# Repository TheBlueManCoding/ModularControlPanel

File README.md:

# ModularControlPanel
Mechanics, PCB and Software for my modular control panel that is used with my cnc machine driven by LinuxCnc

If you need the mechanic parts, just open an issue and tell me.

This bboard delivers:
- 12 Key inputs
- 8 LED outputs driven by 2 boards of these: https://aliexpress.com/item/1005003772569293.html
- 3 ADC inputs
- directly routed inputs for connection to the control cabinet (connected via 15 Pin cable):
  - POWER_KEY or the standby Variant POWER_KEY_MAN, both enable POWER_EN 
  - START_KEY, STOP_KEY, BREAK_KEY
  - input for the ESTOP_LED
  - ESTOP connector
  - 3 Reserve lines
- I2C extension connectors for 3.3 and 5V I2C
- ws28 smart LED connector
- one connector for a MIST System (see https://github.com/TheBlueManCoding/WemosMosfet)

all switches are connected by:
- https://aliexpress.com/item/4000502453714.html
- https://aliexpress.com/item/1005001317075834.html

## Front view of the control panel mockup:

#PCB with some connected switches, leds and the mist cooling controller

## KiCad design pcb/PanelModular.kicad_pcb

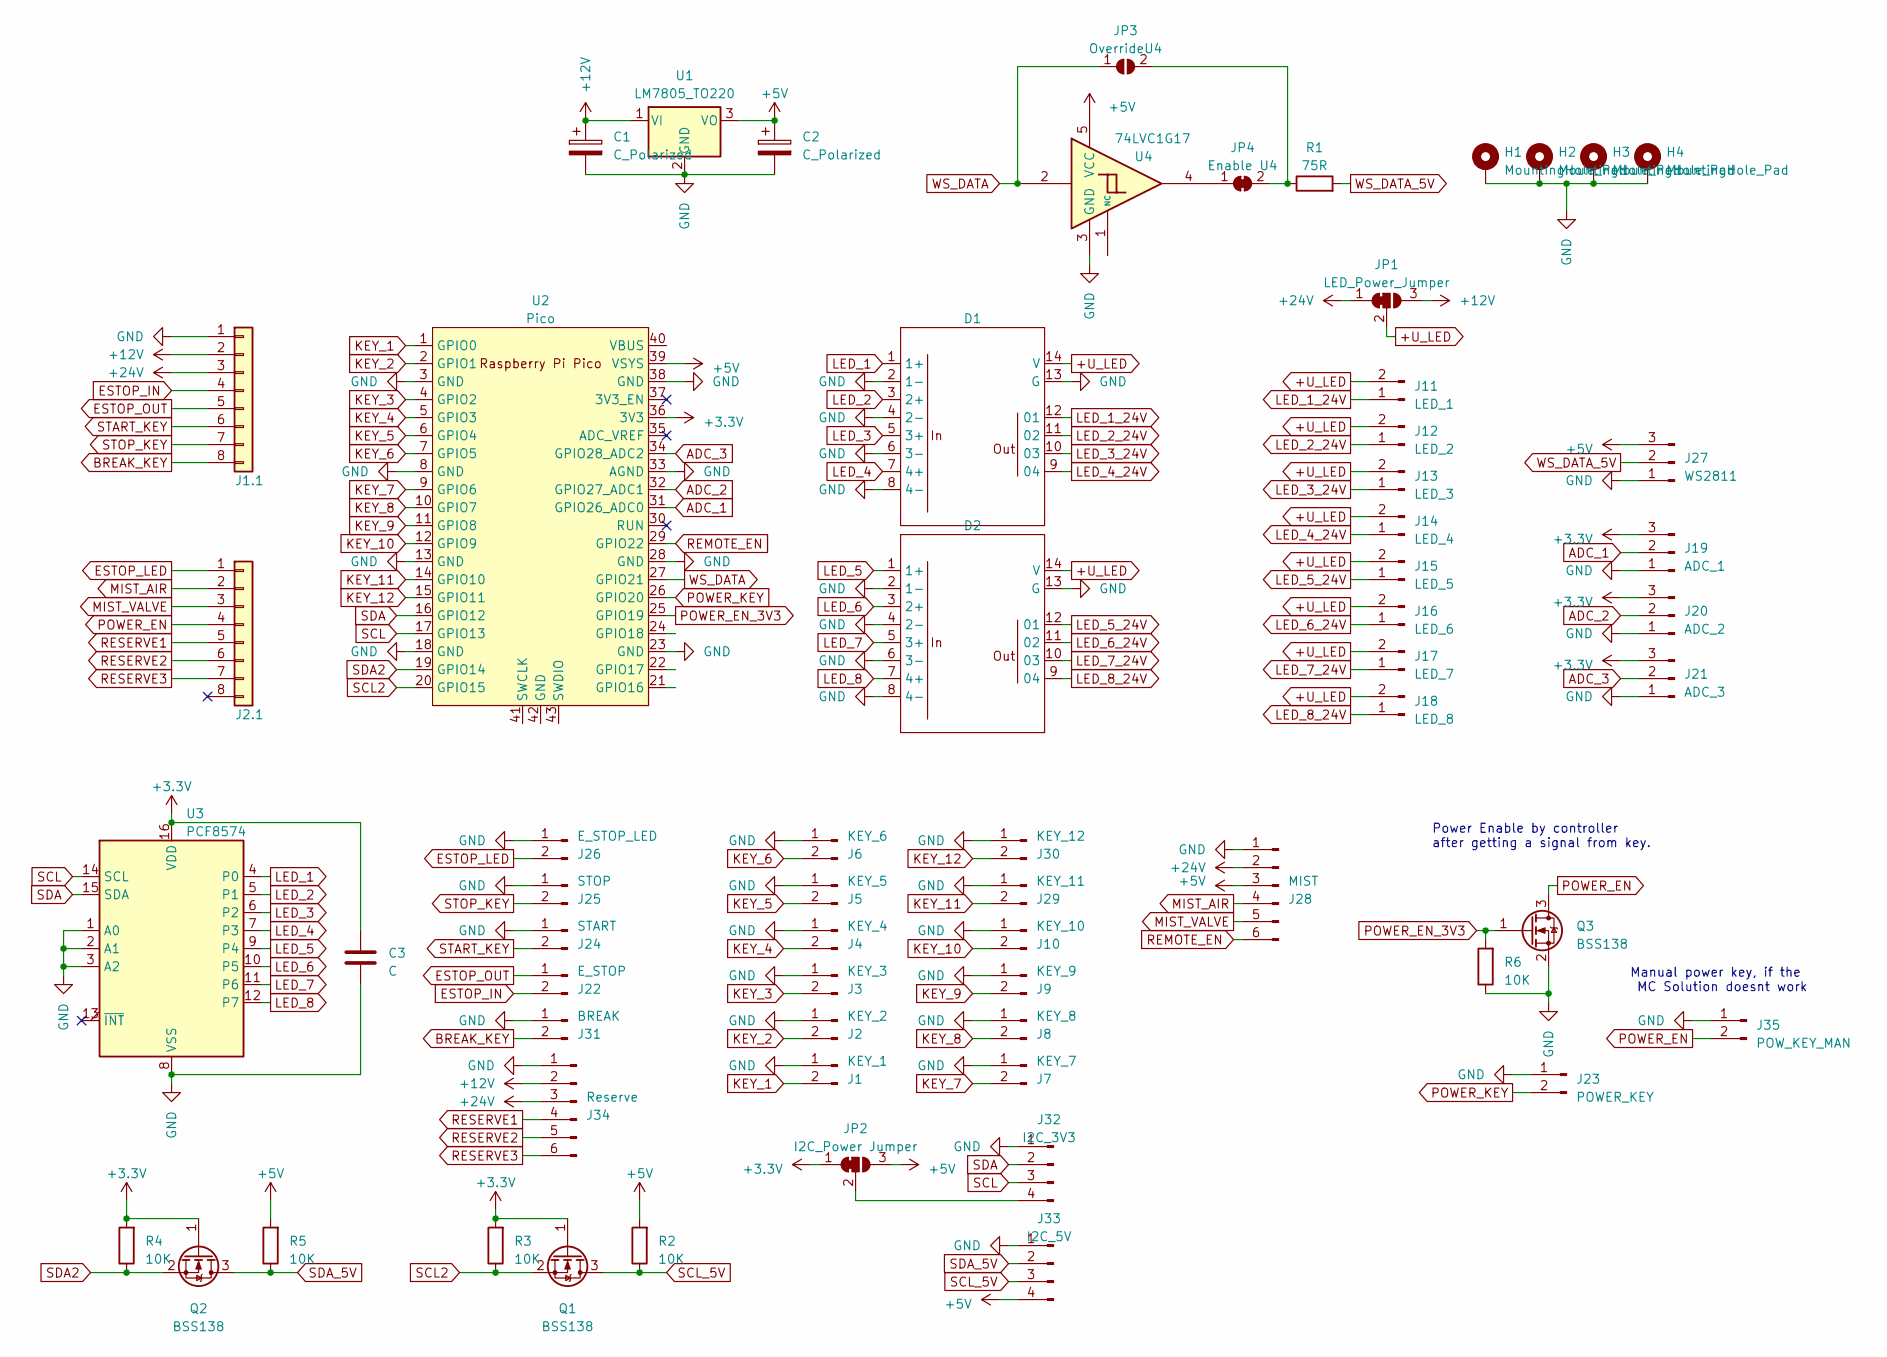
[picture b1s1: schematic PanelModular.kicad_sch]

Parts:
C1, C2: C_Polarized; CP_EIA-6032-28_Kemet-C_Pad2.25x2.35mm_HandSolder
C3: C; C_0805_2012Metric_Pad1.18x1.45mm_HandSolder
D1, D2: OP714A04
H1, H2, H3, H4: MountingHole_Pad; MountingHole_4.3mm_M4_Pad
J1: KEY_1; JST_XH_B2B-XH-A_1x02_P2.50mm_Vertical
J1.1, J2.1: Conn_01x08; TerminalBlock_WAGO_236-408_1x08_P5.00mm_45Degree
J2: KEY_2; JST_XH_B2B-XH-A_1x02_P2.50mm_Vertical
J3: KEY_3; JST_XH_B2B-XH-A_1x02_P2.50mm_Vertical
J4: KEY_4; JST_XH_B2B-XH-A_1x02_P2.50mm_Vertical
J5: KEY_5; JST_XH_B2B-XH-A_1x02_P2.50mm_Vertical
J6: KEY_6; JST_XH_B2B-XH-A_1x02_P2.50mm_Vertical
J7: KEY_7; JST_XH_B2B-XH-A_1x02_P2.50mm_Vertical
J8: KEY_8; JST_XH_B2B-XH-A_1x02_P2.50mm_Vertical
J9: KEY_9; JST_XH_B2B-XH-A_1x02_P2.50mm_Vertical
J10: KEY_10; JST_XH_B2B-XH-A_1x02_P2.50mm_Vertical
J11: LED_1; JST_XH_B2B-XH-A_1x02_P2.50mm_Vertical
J12: LED_2; JST_XH_B2B-XH-A_1x02_P2.50mm_Vertical
J13: LED_3; JST_XH_B2B-XH-A_1x02_P2.50mm_Vertical
J14: LED_4; JST_XH_B2B-XH-A_1x02_P2.50mm_Vertical
J15: LED_5; JST_XH_B2B-XH-A_1x02_P2.50mm_Vertical
J16: LED_6; JST_XH_B2B-XH-A_1x02_P2.50mm_Vertical
J17: LED_7; JST_XH_B2B-XH-A_1x02_P2.50mm_Vertical
J18: LED_8; JST_XH_B2B-XH-A_1x02_P2.50mm_Vertical
J19: ADC_1; JST_XH_B3B-XH-A_1x03_P2.50mm_Vertical
J20: ADC_2; JST_XH_B3B-XH-A_1x03_P2.50mm_Vertical
J21: ADC_3; JST_XH_B3B-XH-A_1x03_P2.50mm_Vertical
J22: E_STOP; JST_XH_B2B-XH-A_1x02_P2.50mm_Vertical
J23: POWER_KEY; JST_XH_B2B-XH-A_1x02_P2.50mm_Vertical
J24: START; JST_XH_B2B-XH-A_1x02_P2.50mm_Vertical
J25: STOP; JST_XH_B2B-XH-A_1x02_P2.50mm_Vertical
J26: E_STOP_LED; JST_XH_B2B-XH-A_1x02_P2.50mm_Vertical
J27: WS2811; JST_XH_B3B-XH-A_1x03_P2.50mm_Vertical
J28: MIST; JST_XH_B6B-XH-A_1x06_P2.50mm_Vertical
J29: KEY_11; JST_XH_B2B-XH-A_1x02_P2.50mm_Vertical
J30: KEY_12; JST_XH_B2B-XH-A_1x02_P2.50mm_Vertical
J31: BREAK; JST_XH_B2B-XH-A_1x02_P2.50mm_Vertical
J32: I2C_3V3; JST_XH_B4B-XH-A_1x04_P2.50mm_Vertical
J33: I2C_5V; JST_XH_B4B-XH-A_1x04_P2.50mm_Vertical
J34: Reserve; JST_XH_B6B-XH-A_1x06_P2.50mm_Vertical
J35: POW_KEY_MAN; JST_XH_B2B-XH-A_1x02_P2.50mm_Vertical
JP1: LED_Power_Jumper; SolderJumper-3_P1.3mm_Bridged12_Pad1.0x1.5mm_NumberLabels
JP2: I2C_Power Jumper; SolderJumper-3_P1.3mm_Bridged12_Pad1.0x1.5mm_NumberLabels
JP3: OverrideU4; SolderJumper-2_P1.3mm_Open_Pad1.0x1.5mm
JP4: Enable U4; SolderJumper-2_P1.3mm_Bridged_Pad1.0x1.5mm
Q1, Q2, Q3: BSS138; SOT-23_Handsoldering
R1: 75R; R_0805_2012Metric_Pad1.20x1.40mm_HandSolder
R2, R3, R4, R5, R6: 10K; R_0805_2012Metric_Pad1.20x1.40mm_HandSolder
U1: LM7805_TO220; TO-220-3_Vertical
U2: Pico; RPi_Pico_SMD_TH
U3: PCF8574; SO-16_7,7x10.2mm_P1.27mm-PCF8574
U4: 74LVC1G17; SOT-23-5_HandSoldering

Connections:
+3.3V: C3.1, J19.3, J20.3, J21.3, JP2.1 (A), Q1.1 (G), Q2.1 (G), R3.2, R4.2, U2.36 (3V3), U3.16 (VDD)
+5V: C2.1, J27.3, J28.3, J33.4, JP2.3 (B), R2.2, R5.2, U1.3 (VO), U2.39 (VSYS), U4.5 (VCC)
+12V: C1.1, J1.1.2, J34.2, JP1.3 (B), U1.1 (VI)
+24V: J1.1.3, J28.2, J34.3, JP1.1 (A)
+U_LED: D1.14 (V), D2.14 (V), J11.2, J12.2, J13.2, J14.2, J15.2, J16.2, J17.2, J18.2, JP1.2 (C)
ADC_1: J19.2, U2.31 (GPIO26_ADC0)
ADC_2: J20.2, U2.32 (GPIO27_ADC1)
ADC_3: J21.2, U2.34 (GPIO28_ADC2)
BREAK_KEY: J1.1.8, J31.2
ESTOP_IN: J1.1.4, J22.2
ESTOP_LED: J2.1.1, J26.2
ESTOP_OUT: J1.1.5, J22.1
GND: C1.2, C2.2, C3.2, D1.2 (1-), D1.4 (2-), D1.6 (3-), D1.8 (4-), D1.13 (G), D2.2 (1-), D2.4 (2-), D2.6 (3-), D2.8 (4-), D2.13 (G), H1.1, H2.1, H3.1, H4.1, J1.1, J1.1.1, J2.1, J3.1, J4.1, J5.1, J6.1, J7.1, J8.1, J9.1, J10.1, J19.1, J20.1, J21.1, J23.1, J24.1, J25.1, J26.1, J27.1, J28.1, J29.1, J30.1, J31.1, J32.1, J33.1, J34.1, J35.1, Q3.2 (S), R6.1, U1.2 (GND), U2.3 (GND), U2.8 (GND), U2.13 (GND), U2.18 (GND), U2.23 (GND), U2.28 (GND), U2.33 (AGND), U2.38 (GND), U3.1 (A0), U3.2 (A1), U3.3 (A2), U3.8 (VSS), U4.3 (GND)
KEY_1: J1.2, U2.1 (GPIO0)
KEY_2: J2.2, U2.2 (GPIO1)
KEY_3: J3.2, U2.4 (GPIO2)
KEY_4: J4.2, U2.5 (GPIO3)
KEY_5: J5.2, U2.6 (GPIO4)
KEY_6: J6.2, U2.7 (GPIO5)
KEY_7: J7.2, U2.9 (GPIO6)
KEY_8: J8.2, U2.10 (GPIO7)
KEY_9: J9.2, U2.11 (GPIO8)
KEY_10: J10.2, U2.12 (GPIO9)
KEY_11: J29.2, U2.14 (GPIO10)
KEY_12: J30.2, U2.15 (GPIO11)
LED_1: D1.1 (1+), U3.4 (P0)
LED_1_24V: D1.12 (01), J11.1
LED_2: D1.3 (2+), U3.5 (P1)
LED_2_24V: D1.11 (02), J12.1
LED_3: D1.5 (3+), U3.6 (P2)
LED_3_24V: D1.10 (03), J13.1
LED_4: D1.7 (4+), U3.7 (P3)
LED_4_24V: D1.9 (04), J14.1
LED_5: D2.1 (1+), U3.9 (P4)
LED_5_24V: D2.12 (01), J15.1
LED_6: D2.3 (2+), U3.10 (P5)
LED_6_24V: D2.11 (02), J16.1
LED_7: D2.5 (3+), U3.11 (P6)
LED_7_24V: D2.10 (03), J17.1
LED_8: D2.7 (4+), U3.12 (P7)
LED_8_24V: D2.9 (04), J18.1
MIST_AIR: J2.1.2, J28.4
MIST_VALVE: J2.1.3, J28.5
unnamed: J32.4, JP2.2 (C)
unnamed: JP3.2 (B), JP4.2 (B), R1.1
unnamed: JP4.1 (A), U4.4
POWER_EN: J2.1.4, J35.2, Q3.3 (D)
POWER_EN_3V3: Q3.1 (G), R6.2, U2.25 (GPIO19)
POWER_KEY: J23.2, U2.26 (GPIO20)
REMOTE_EN: J28.6, U2.29 (GPIO22)
RESERVE1: J2.1.5, J34.4
RESERVE2: J2.1.6, J34.5
RESERVE3: J2.1.7, J34.6
SCL: J32.3, U2.17 (GPIO13), U3.14 (SCL)
SCL2: Q1.2 (S), R3.1, U2.20 (GPIO15)
SCL_5V: J33.3, Q1.3 (D), R2.1
SDA: J32.2, U2.16 (GPIO12), U3.15 (SDA)
SDA2: Q2.2 (S), R4.1, U2.19 (GPIO14)
SDA_5V: J33.2, Q2.3 (D), R5.1
START_KEY: J1.1.6, J24.2
STOP_KEY: J1.1.7, J25.2
WS_DATA: JP3.1 (A), U2.27 (GPIO21), U4.2
WS_DATA_5V: J27.2, R1.2

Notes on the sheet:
Power Enable by controller after getting a signal from key.
Manual power key, if the MC Solution doesnt work

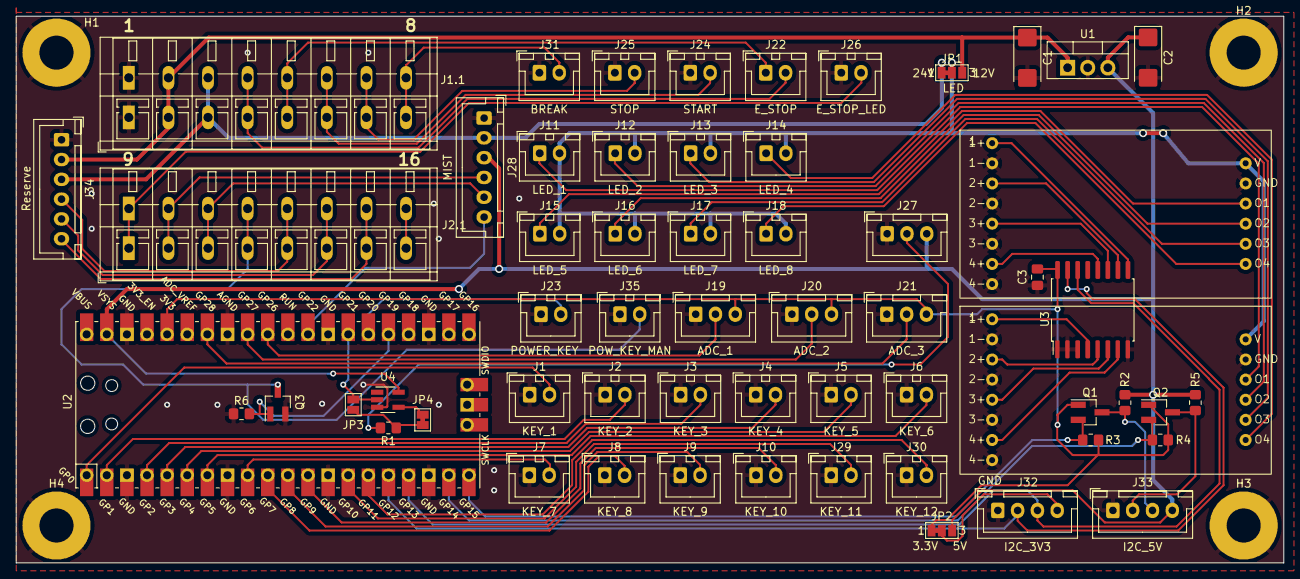
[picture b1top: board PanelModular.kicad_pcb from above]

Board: 2 copper layers, 160.0 x 69.0 mm, 63 parts (0 on the bottom side), 63 nets.

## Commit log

2023-05-17 First complete version of pcb
2023-05-22 I2C ready version
2023-07-05 The first ordered Version, missing i2c pullups and wrong i2c connected to external
2023-07-06 Revert "The first ordered Version, missing i2c pullups and wrong i2c connected to external"
    This reverts commit 4b4ee199a77fa0146eabba4f0e18928ce2f89e34.
2023-07-06 Really the first ordered Version, missing i2c pullups and wrong i2c connected to external
2023-07-18 All Hardware of PCB working
2023-07-23 Wifi and Mqtt tested
2023-11-12 Source files: - project update for cmsis-dap debugger (pico debugger) - Implemented input classes for digital and analog - digital inputs can toggle and directly connect to a digital output to connec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
    PCB users:
    - the PCF8574 i planned for the PCB doesn't workin my design as it can only sing. I use the TCA9534 which works fine.
2023-11-12 added images
2023-12-28 Moved wifi credentials to: SecretSettings.h, build your own with SecretSettings.example.h
    Reworked Wifi/Mqtt stuff and packed into Mqtt.h
    Reworked Inputs:
    - New AbstractDigitalInput class that allows direct connection to outputs (e.g. you can connect the led directly to the button)
    Reworked outputs:
    - inverting the output now done in AbstractDigitalOutput
    main.cpp:
